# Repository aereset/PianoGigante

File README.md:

# PianoGigante
En este repo se puede encontrar el programa en PureData que utilizamos para el Piano Gigante y los archivos de la PCB para EAGLE en caso de que a alguien le resulte de utilidad.

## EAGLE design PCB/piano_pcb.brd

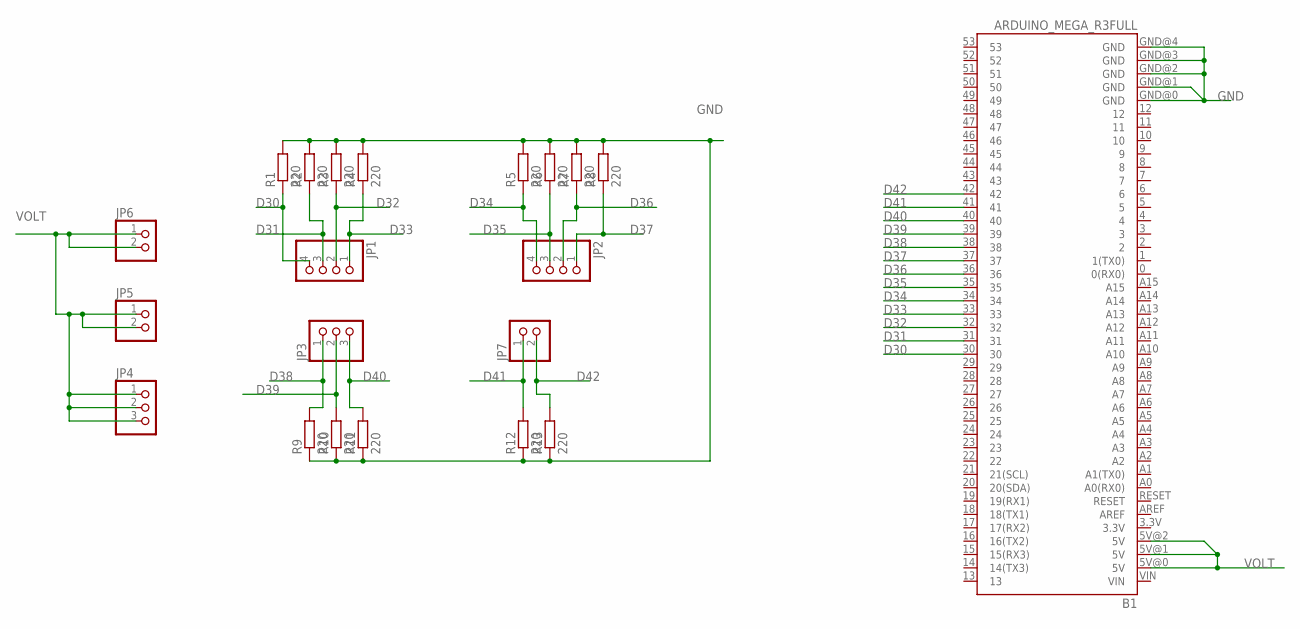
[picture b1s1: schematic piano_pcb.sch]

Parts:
B1: ARDUINO_MEGA_R3FULL; ARDUINO_MEGA
JP1, JP2: PINHD-1X4; 1X04
JP3, JP4: PINHD-1X3; 1X03
JP5, JP6, JP7: PINHD-1X2; 1X02
R1, R2, R3, R4, R5, R6, R7, R8, R9, R10, R11, R12, R13: 220; 0204/5

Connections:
D30: B1.30, JP1.4, R1.1
D31: B1.31, JP1.3, R2.1
D32: B1.32, JP1.2, R3.1
D33: B1.33, JP1.1, R4.1
D34: B1.34, JP2.4, R5.1
D35: B1.35, JP2.3, R6.1
D36: B1.36, JP2.2, R7.1
D37: B1.37, JP2.1, R8.1
D38: B1.38, JP3.1, R9.2
D39: B1.39, JP3.2, R10.2
D40: B1.40, JP3.3, R11.2
D41: B1.41, JP7.1, R12.2
D42: B1.42, JP7.2, R13.2
GND: B1.GND@0 (GND), B1.GND@1 (GND), B1.GND@2 (GND), B1.GND@3 (GND), B1.GND@4 (GND), R1.2, R2.2, R3.2, R4.2, R5.2, R6.2, R7.2, R8.2, R9.1, R10.1, R11.1, R12.1, R13.1
VOLT: B1.5V@0 (5V), B1.5V@1 (5V), B1.5V@2 (5V), JP4.1, JP4.2, JP4.3, JP5.1, JP5.2, JP6.1, JP6.2

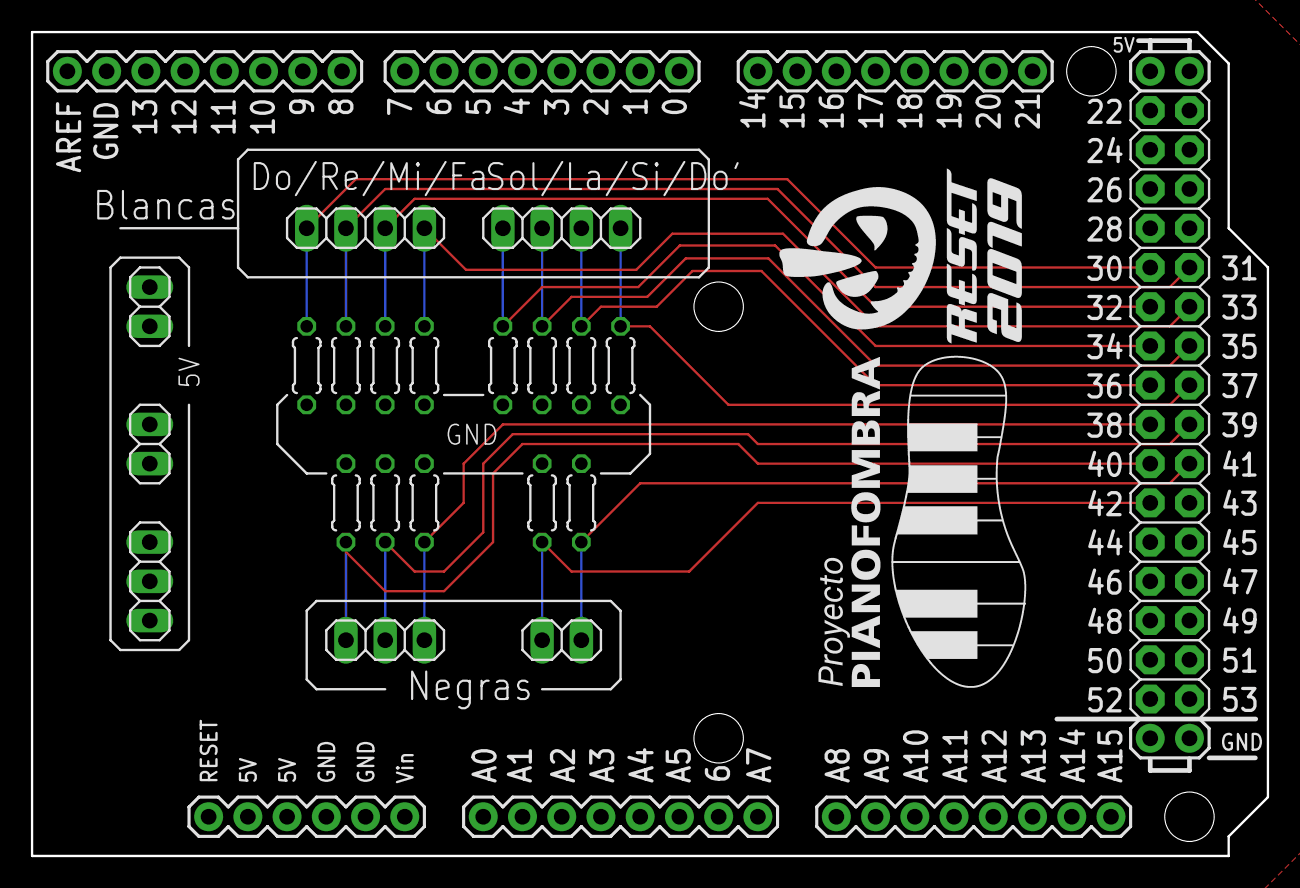
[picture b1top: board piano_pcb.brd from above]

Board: 2 copper layers, 80.0 x 53.3 mm, 23 parts (1 on the bottom side), 15 nets.

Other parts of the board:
U$1, U$2: Z_LOGO_PIANO

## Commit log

2020-03-23 PCB subida

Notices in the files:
parts and their libraries:
SparkFun-Boards: Licensing: Creative Commons ShareAlike 4.0 International - https://creativecommons.org/licenses/by-sa/4.0
